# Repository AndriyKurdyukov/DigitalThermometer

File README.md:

# DigitalThermometer

## Description
A simple digital thermometer with hardware and firmware made from scratch. Kicad was used for PCB design and STM Cube IDE for firmware.

## Why?
I  wanted to refresh my electronics skills and decided to make a simple first KICAD project combining both firmware and hardware. I am obviously more familiar with the firmware side of things because of my job.

## Hardware
An STM32F030F4P6 microcontroller (4 KB RAM, 16 KB FLASH) was used to read out temperature values from an TMP117 temperature sensor over I2C.
A Newhaven NHD-C0220BIZ LCD display was used for displaying temperature values, using I2C communication as well.

## Firmware
A simple while loop reading out values from temperature sensor and sending them to the display, no RTOS used and everything in blocking mode. Since I2C HAL bloats memory so much, I rewrote it using Lower Layer. Maybe I should do the same for the GPIO.

Fimrware can be flashed on the microcontroller with any Nucleo board using ST-Link over SWD(see connector J3 on the board).

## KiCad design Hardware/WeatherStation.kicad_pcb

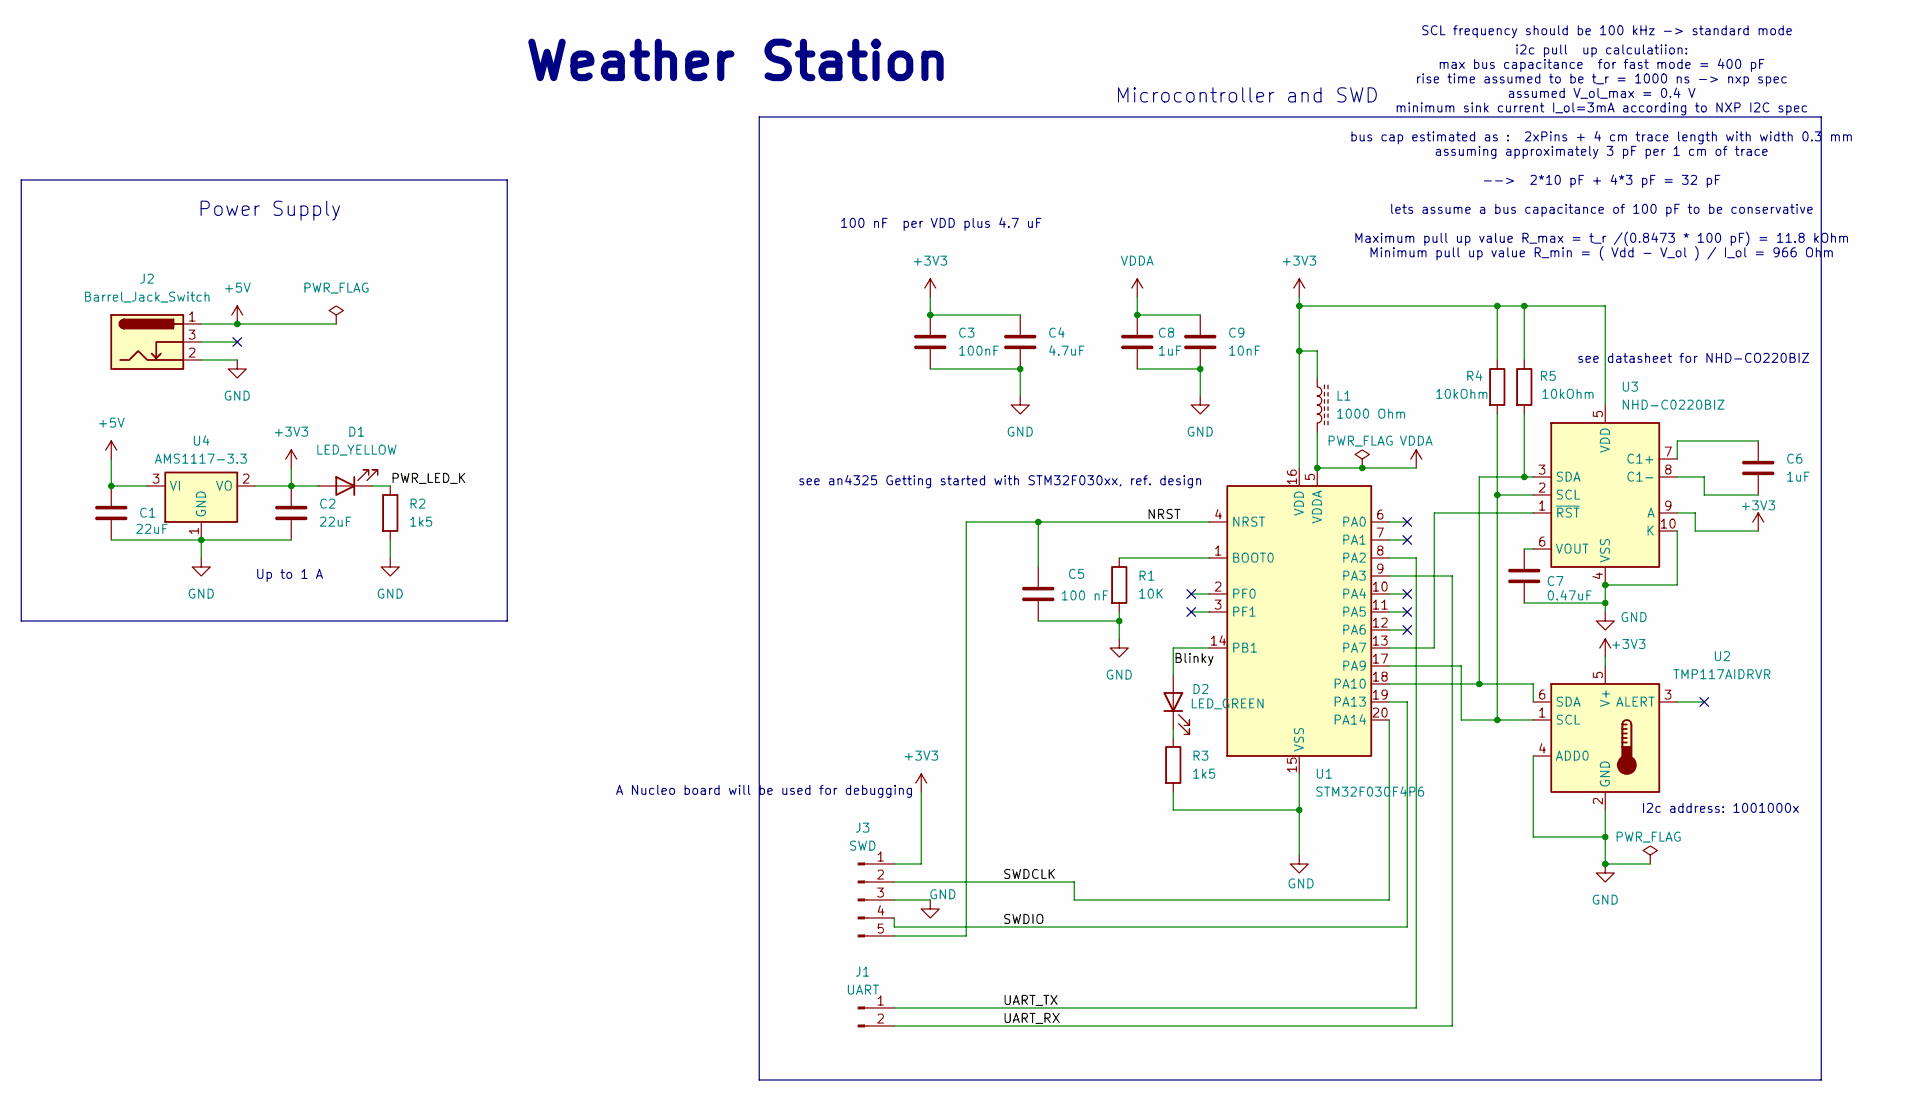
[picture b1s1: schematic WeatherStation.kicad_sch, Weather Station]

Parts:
C1, C2: 22uF; C_0805_2012Metric
C3: 100nF; C_0402_1005Metric
C4: 4.7uF; C_0603_1608Metric
C5: 100 nF; C_0402_1005Metric
C6: 1uF; C_0603_1608Metric
C7: 0.47uF; C_0402_1005Metric
C8: 1uF; C_0402_1005Metric
C9: 10nF; C_0402_1005Metric
D1: LED_YELLOW; LED_0603_1608Metric
D2: LED_GREEN; LED_0603_1608Metric
J1: UART; PinSocket_1x02_P2.54mm_Vertical
J2: Barrel_Jack_Switch; Wurth_Barreljack_694106301002
J3: SWD; PinSocket_1x05_P2.54mm_Vertical
L1: 1000 Ohm; L_0603_1608Metric
R1: 10K; R_0402_1005Metric
R2, R3: 1k5; R_0402_1005Metric
R4, R5: 10kOhm; R_0402_1005Metric
U1: STM32F030F4P6; TSSOP-20_4.4x6.5mm_P0.65mm
U2: TMP117AIDRVR; WSON-6-1EP_2x2mm_P0.65mm_EP1x1.6mm
U3: NHD-C0220BIZ; NHD-C0220BiZ
U4: AMS1117-3.3; SOT-223-3_TabPin2

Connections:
+3V3: C2.1, C3.1, C4.1, D1.2 (A), J3.1, L1.1, R4.1, R5.1, U1.16 (VDD), U2.5 (V+), U3.5 (VDD), U3.9 (A), U4.2 (VO)
+5V: C1.1, J2.1, U4.3 (VI)
/Blinky: D2.2 (A), U1.14 (PB1)
/NRST: C5.1, J3.5, U1.4 (NRST)
/PWR_LED_K: D1.1 (K), R2.1
/SWDCLK: J3.2, U1.20 (PA14)
/SWDIO: J3.4, U1.19 (PA13)
/UART_RX: J1.2, U1.9 (PA3)
/UART_TX: J1.1, U1.8 (PA2)
GND: C1.2, C2.2, C3.2, C4.2, C5.2, C7.2, C8.2, C9.2, J2.2, J3.3, R1.2, R2.2, R3.2, U1.15 (VSS), U2.2 (GND), U2.4 (ADD0), U3.4 (VSS), U3.10 (K), U4.1 (GND)
unnamed: D2.1 (K), R3.1
unnamed: R1.1, U1.1 (BOOT0)
unnamed: U1.13 (PA7), U3.1 (~RST)
unnamed: R4.2, U1.17 (PA9), U2.1 (SCL), U3.2 (SCL)
unnamed: R5.2, U1.18 (PA10), U2.6 (SDA), U3.3 (SDA)
unnamed: C6.2, U3.7 (C1+)
unnamed: C6.1, U3.8 (C1-)
unnamed: C7.1, U3.6 (VOUT)
VDDA: C8.1, C9.1, L1.2, U1.5 (VDDA)

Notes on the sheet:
A Nucleo board will be used for debugging
SCL frequency should be 100 kHz -> standard mode
Up to 1 A
Microcontroller and SWD
I2c address: 1001000x
Power Supply
i2c pull up calculatiion: max bus capacitance for fast mode = 400 pF rise time assumed to be t_r = 1000 ns -> nxp spec assumed V_ol_max = 0.4 V minimum sink current I_ol=3mA according to NXP I2C spec bus cap estimated as : 2xPins + 4 cm trace length with width 0.3 mm assuming approximately 3 pF per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
see datasheet for NHD-CO220BIZ
see an4325 Getting started with STM32F030xx, ref. design
Weather Station
100 nF per VDD plus 4.7 uF

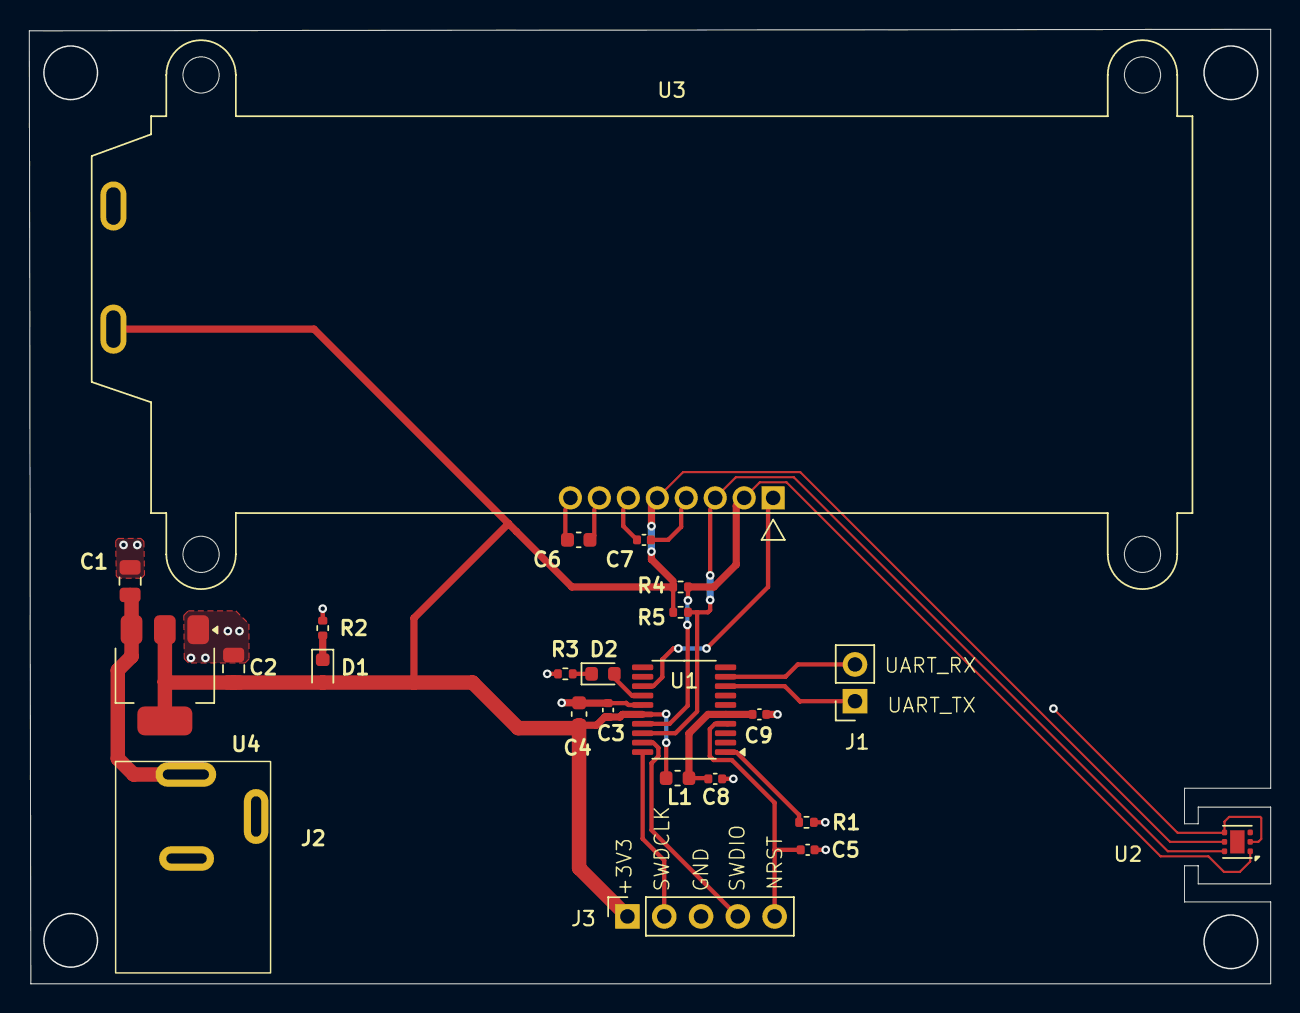
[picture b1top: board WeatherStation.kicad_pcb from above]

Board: 2 copper layers, 85.7 x 65.9 mm, 24 parts (0 on the bottom side), 19 nets.

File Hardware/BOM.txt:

Reference	Qty	Value	DNP	Exclude from BOM	Exclude from Board	Footprint	Datasheet
C1,C2	2	22uF				Capacitor_SMD:C_0805_2012Metric	~
C3	1	100nF				Capacitor_SMD:C_0402_1005Metric	~
C4	1	4.7uF				Capacitor_SMD:C_0603_1608Metric	~
C5	1	100 nF				Capacitor_SMD:C_0402_1005Metric	~
C6	1	1uF				Capacitor_SMD:C_0603_1608Metric	~
C7	1	0.47uF				Capacitor_SMD:C_0402_1005Metric	~
C8	1	1uF				Capacitor_SMD:C_0402_1005Metric	~
C9	1	10nF				Capacitor_SMD:C_0402_1005Metric	~
D1	1	LED_YELLOW				LED_SMD:LED_0603_1608Metric	~
D2	1	LED_GREEN				LED_SMD:LED_0603_1608Metric	~
J1	1	UART				Connector_PinSocket_2.54mm:PinSocket_1x02_P2.54mm_Vertical	~
J2	1	Barrel_Jack_Switch				WURTH_DC_BUCHSE:Wurth_Barreljack_694106301002	~
J3	1	SWD				Connector_PinSocket_2.54mm:PinSocket_1x05_P2.54mm_Vertical	~
L1	1	1000 Ohm				Inductor_SMD:L_0603_1608Metric	~
R1	1	10K				Resistor_SMD:R_0402_1005Metric	~
R2,R3	2	1k5				Resistor_SMD:R_0402_1005Metric	~
R4,R5	2	10kOhm				Resistor_SMD:R_0402_1005Metric	~
U1	1	STM32F030F4P6				Package_SO:TSSOP-20_4.4x6.5mm_P0.65mm	https://www.st.com/resource/en/datasheet/stm32f030f4.pdf
U2	1	TMP117AIDRVR				Package_SON:WSON-6-1EP_2x2mm_P0.65mm_EP1x1.6mm	https://www.ti.com/lit/ds/symlink/tmp117.pdf
U3	1	NHD-C0220BIZ				Display:NHD-C0220BiZ	http://www.newhavendisplay.com/specs/NHD-C0220BiZ-FSW-FBW-3V3M.pdf
U4	1	AMS1117-3.3				Package_TO_SOT_SMD:SOT-223-3_TabPin2	http://www.advanced-monolithic.com/pdf/ds1117.pdf
